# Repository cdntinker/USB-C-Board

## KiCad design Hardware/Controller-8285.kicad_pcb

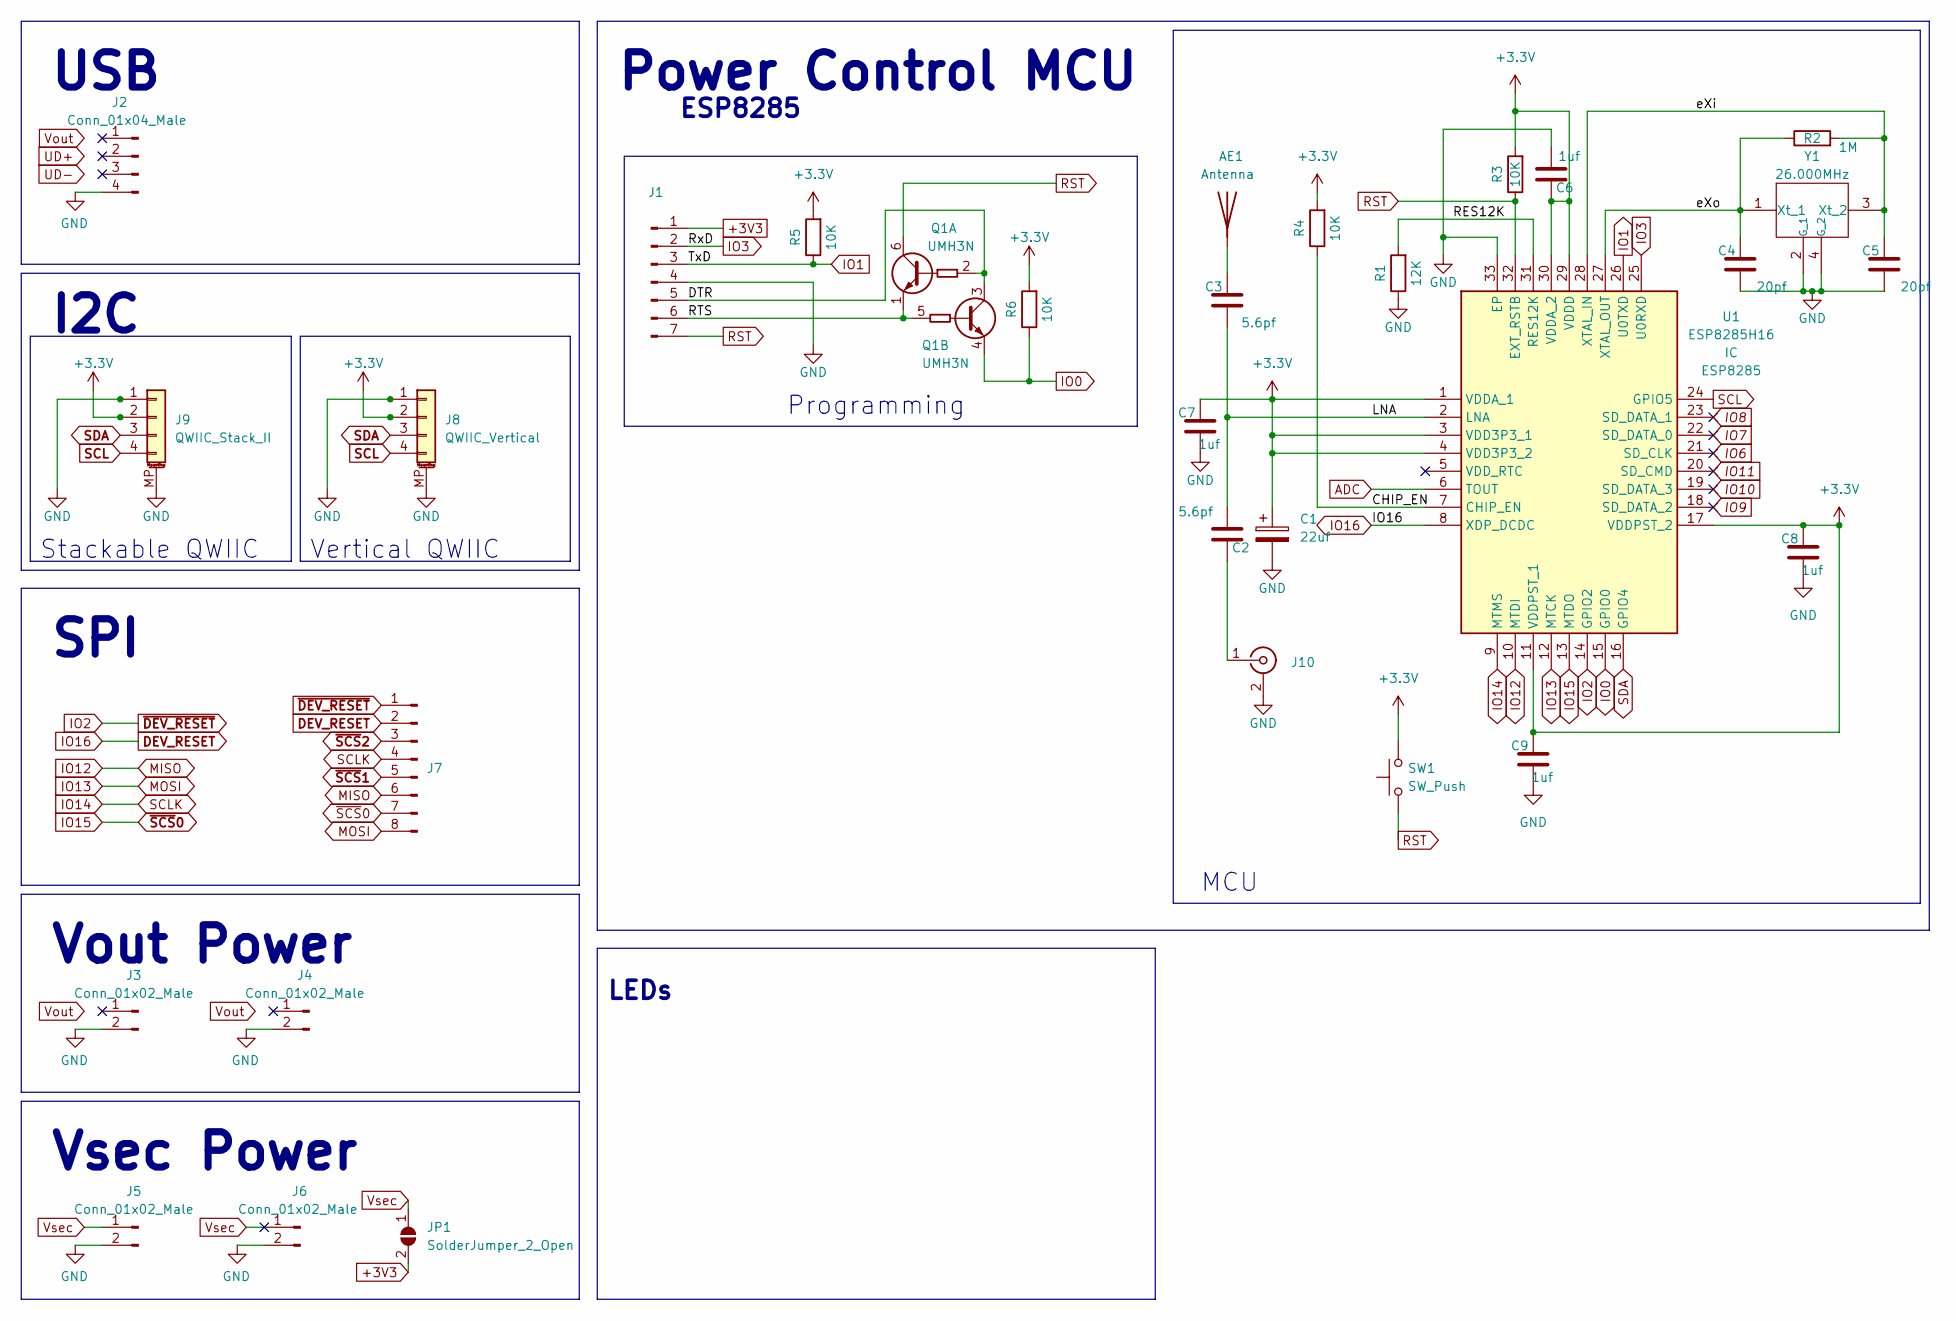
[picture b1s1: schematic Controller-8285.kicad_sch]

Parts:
AE1: Antenna; Texas_SWRA117D_2.4GHz_Left
C1: 22uf; CP_EIA-6032-28-Tantalumm_HandSolder; LCSC C89246
C2, C3: 5.6pf; C_0603_1608Metric; LCSC C162238
C4, C5: 20pf; C_0603_1608Metric; LCSC C325469
C6, C7, C8, C9: 1uf; C_0603_1608Metric; LCSC C559769
J1: Conn_01x07_Male; Board_Stacker_7
J2: Conn_01x04_Male; Board_Stacker_4
J3, J4, J5, J6: Conn_01x02_Male; Board_Stacker_2
J7: Conn_01x08_Male; PinHeader_2x04_P1.27mm_Vertical; LCSC C2881786 + C2684732
J8: QWIIC_Vertical; LCSC C145961
J9: QWIIC_Stack_II; LCSC C145956, C2881513, C2938401
J10: Conn_Coaxial; U.FL_Molex_MCRF_73412-0110_Vertical; LCSC C88373
JP1: SolderJumper_2_Open; SolderJumper-2_P_Open_Rounded_skinny
Q1: UMH3N; SOT-363_SC-70-6; LCSC C62892
R1: 12K; R_0603_1608Metric; LCSC C22790
R2: 1M; R_0603_1608Metric; LCSC C22935
R3, R4, R5, R6: 10K; R_0603_1608Metric; LCSC C25804
SW1: SW_Push; SW_Push_TS273014TP; LCSC C2858276
U1: ESP8285H16; QFN50P500X500X90-33N-D; Manufacturer_Part_Number ESP8285; LCSC C967019
Y1: 26.000MHz; ABM825000MHz10B1UT; LCSC C2149083

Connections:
/CHIP_EN: R4.1, U1.7 (CHIP_EN)
/DTR: J1.5, Q1.2 (B1), Q1.3 (C2)
/LNA: C2.1, C3.1, U1.2 (LNA)
/RES12K: R1.2, U1.31 (RES12K)
/RTS: J1.6, Q1.1 (E1), Q1.5 (B2)
/eXi: C5.2, R2.2, U1.28 (XTAL_IN), Y1.3 (Xt_2)
/eXo: C4.2, R2.1, U1.27 (XTAL_OUT), Y1.1 (Xt_1)
ADC: U1.6 (TOUT)
DEV_RESET: J7.2, U1.8 (XDP_DCDC)
GND: C1.2, C4.1, C5.1, C6.1, C7.1, C8.1, C9.1, J1.4, J2.4, J3.2, J4.2, J5.2, J6.2, J8.1, J8.MP (MountPin), J9.1, J9.MP (MountPin), J10.2 (Ext), R1.1, U1.33 (EP), Y1.2 (G_1), Y1.4 (G_2)
IO0: Q1.4 (E2), R6.1, U1.15 (GPIO0)
IO1: J1.3, R5.1, U1.26 (U0TXD)
IO2: J7.1, U1.14 (GPIO2)
IO3: J1.2, U1.25 (U0RXD)
IO6: U1.21 (SD_CLK)
IO7: U1.22 (SD_DATA_0)
IO8: U1.23 (SD_DATA_1)
IO9: U1.18 (SD_DATA_2)
IO10: U1.19 (SD_DATA_3)
IO11: U1.20 (SD_CMD)
IO12: J7.6, U1.10 (MTDI)
IO13: J7.8, U1.12 (MTCK)
IO14: J7.4, U1.9 (MTMS)
IO15: J7.7, U1.13 (MTDO)
unnamed: AE1.1, C3.2
unnamed: C2.2, J10.1 (In)
RST: J1.7, Q1.6 (C1), R3.1, SW1.1, U1.32 (EXT_RSTB)
SCL: J8.4, J9.4, U1.24 (GPIO5)
SDA: J8.3, J9.3, U1.16 (GPIO4)
Vsec: J5.1, J6.1, JP1.1 (A)
~SCS1: J7.5
~SCS2: J7.3

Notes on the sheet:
I2C
MCU
Vertical QWIIC
Vsec Power
ESP8285
Power Control MCU
USB
SPI
Programming
Vout Power
Stackable QWIIC
LEDs

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
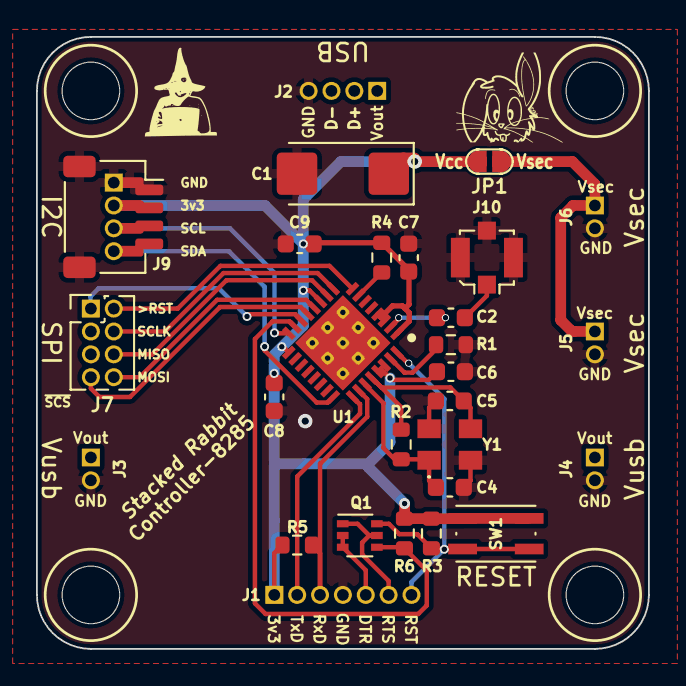
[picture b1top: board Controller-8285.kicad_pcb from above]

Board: 2 copper layers, 34.0 x 34.0 mm, 28 parts (0 on the bottom side), 23 nets.

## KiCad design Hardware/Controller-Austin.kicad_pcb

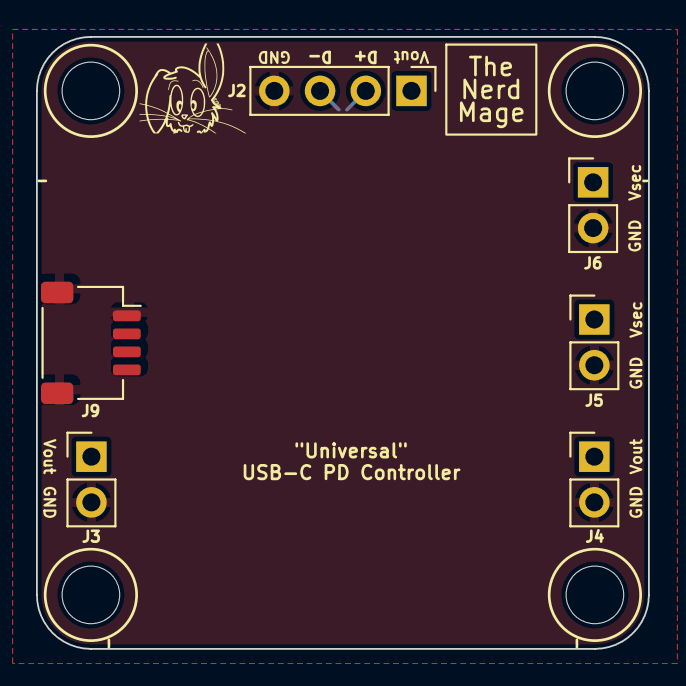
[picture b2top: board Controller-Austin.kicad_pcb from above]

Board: 2 copper layers, 34.0 x 34.0 mm, 6 parts (0 on the bottom side), 3 nets.

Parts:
J2: Conn_01x04_Male; PinHeader_1x04_P2.54mm_Vertical
J3, J4, J5, J6: Conn_01x02_Male; PinHeader_1x02_P2.54mm_Vertical
J9: Conn_01x04_MountingPin; JST_SH_SM04B-SRSS-TB_1x04-1MP_P1.00mm_Horizontal

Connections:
GND: J2.4, J3.2, J4.2, J5.2, J6.2, J9.1, J9.MP (MountPin)
Vout: J2.1, J3.1, J4.1
Vsec: J5.1, J6.1

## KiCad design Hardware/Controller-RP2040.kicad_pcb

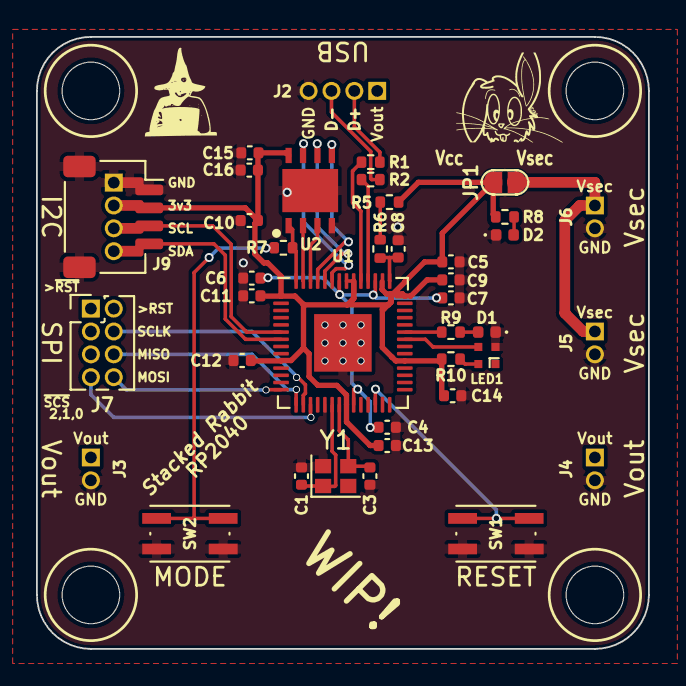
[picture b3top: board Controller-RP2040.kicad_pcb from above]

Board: 2 copper layers, 34.0 x 34.0 mm, 39 parts (0 on the bottom side), 31 nets.

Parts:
C1, C3: 20p; C_0402_1005Metric
C4, C5, C8, C15: 2u2; C_0402_1005Metric
C6, C7, C9, C10, C11, C12, C13, C14, C16: 100n; C_0402_1005Metric
D1, D2: LED; LED_0402_1005Metric
J2: Conn_01x04_Male; Board_Stacker_4
J3, J4, J5, J6: Conn_01x02_Male; Board_Stacker_2
J7: Conn_01x08_Male; PinHeader_2x04_P1.27mm_Vertical
J9: QWIIC_Stack_II
JP1: SolderJumper_2_Open; SolderJumper-2_P_Open_Rounded_skinny
LED1: XL-1010RGBC-WS2812B; XL1010RGBCWS2812B
R1, R2: 27; R_0402_1005Metric
R5: 200; R_0402_1005Metric
R6: 1; R_0402_1005Metric
R7: 1k; R_0402_1005Metric
R8: 2k2; R_0402_1005Metric
R9: 470; R_0402_1005Metric
R10: ???; R_0402_1005Metric
SW1, SW2: SW_Push; SW_Push_TS273014TP
U1: RP2040; QFN-56-1EP_7x7mm_P0.4mm_EP3.2x3.2mm
U2: W25Q32JVXGIQ; SON80P400X400X50-9N
Y1: 12MHz; Crystal_SMD_2016-4Pin_2.0x1.6mm

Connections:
+1V1: C4.2, C6.1, C7.1, U1.23 (DVDD), U1.45 (VREG_VOUT), U1.50 (DVDD)
+3V3: C5.1, C9.1, C10.1, C11.1, C12.1, C13.1, C14.1, C15.2, C16.1, J9.2, JP1.2 (B), R5.2, R8.1, R10.1, U1.1 (IOVDD), U1.10 (IOVDD), U1.22 (IOVDD), U1.33 (IOVDD), U1.42 (IOVDD), U1.44 (VREG_IN), U1.48 (USB_VDD), U1.49 (IOVDD), U2.8 (VCC)
/USB_DM: R2.2, U1.46 (USB_DM)
/USB_DP: R1.2, U1.47 (USB_DP)
/Xout: C3.1, U1.21 (XOUT), Y1.3
ADC_REF: R5.1, R6.2
BootMode: R7.2, SW2.2
GND: C1.2, C3.2, C4.1, C5.2, C6.2, C7.2, C8.1, C9.2, C10.2, C11.2, C12.2, C13.2, C14.2, C15.1, C16.2, D1.1 (K), D2.1 (K), J2.4, J3.2, J4.2, J5.2, J6.2, J9.1, J9.MP (MountPin), LED1.3 (GND), SW1.1, SW2.1, U1.19 (TESTEN), U1.57 (GND), U2.4 (GND), U2.9 (EP), Y1.4
MISO: J7.6, U1.15 (GPIO12)
MOSI: J7.8, U1.14 (GPIO11)
unnamed: C1.1, U1.20 (XIN), Y1.1
unnamed: C8.2, R6.1, U1.43 (ADC_AVDD)
unnamed: D1.2 (A), R9.2
unnamed: D2.2 (A), R8.2
unnamed: LED1.2 (VDD), R10.2
QSPI SS: R7.1, U1.56 (QSPI_SS), U2.1 (~CS)
QSPI_SCLK: U1.52 (QSPI_SCLK), U2.6 (CLK)
QSPI_SD0: U1.53 (QSPI_SD0), U2.5 (DI(IO0))
QSPI_SD1: U1.55 (QSPI_SD1), U2.2 (DO(IO1))
QSPI_SD2: U1.54 (QSPI_SD2), U2.3 (IO2)
QSPI_SD3: U1.51 (QSPI_SD3), U2.7 (IO3)
Reset: SW1.2, U1.26 (RUN)
SCL: J9.4, U1.7 (GPIO5)
SCLK: J7.4, U1.16 (GPIO13)
SDA: J9.3, U1.6 (GPIO4)
UD+: J2.2, R1.1
UD-: J2.3, R2.1
Vsec: J5.1, J6.1, JP1.1 (A)
io14: J7.7, U1.17 (GPIO14)
io24: LED1.4 (DI), U1.36 (GPIO24)
io25: R9.1, U1.37 (GPIO25)

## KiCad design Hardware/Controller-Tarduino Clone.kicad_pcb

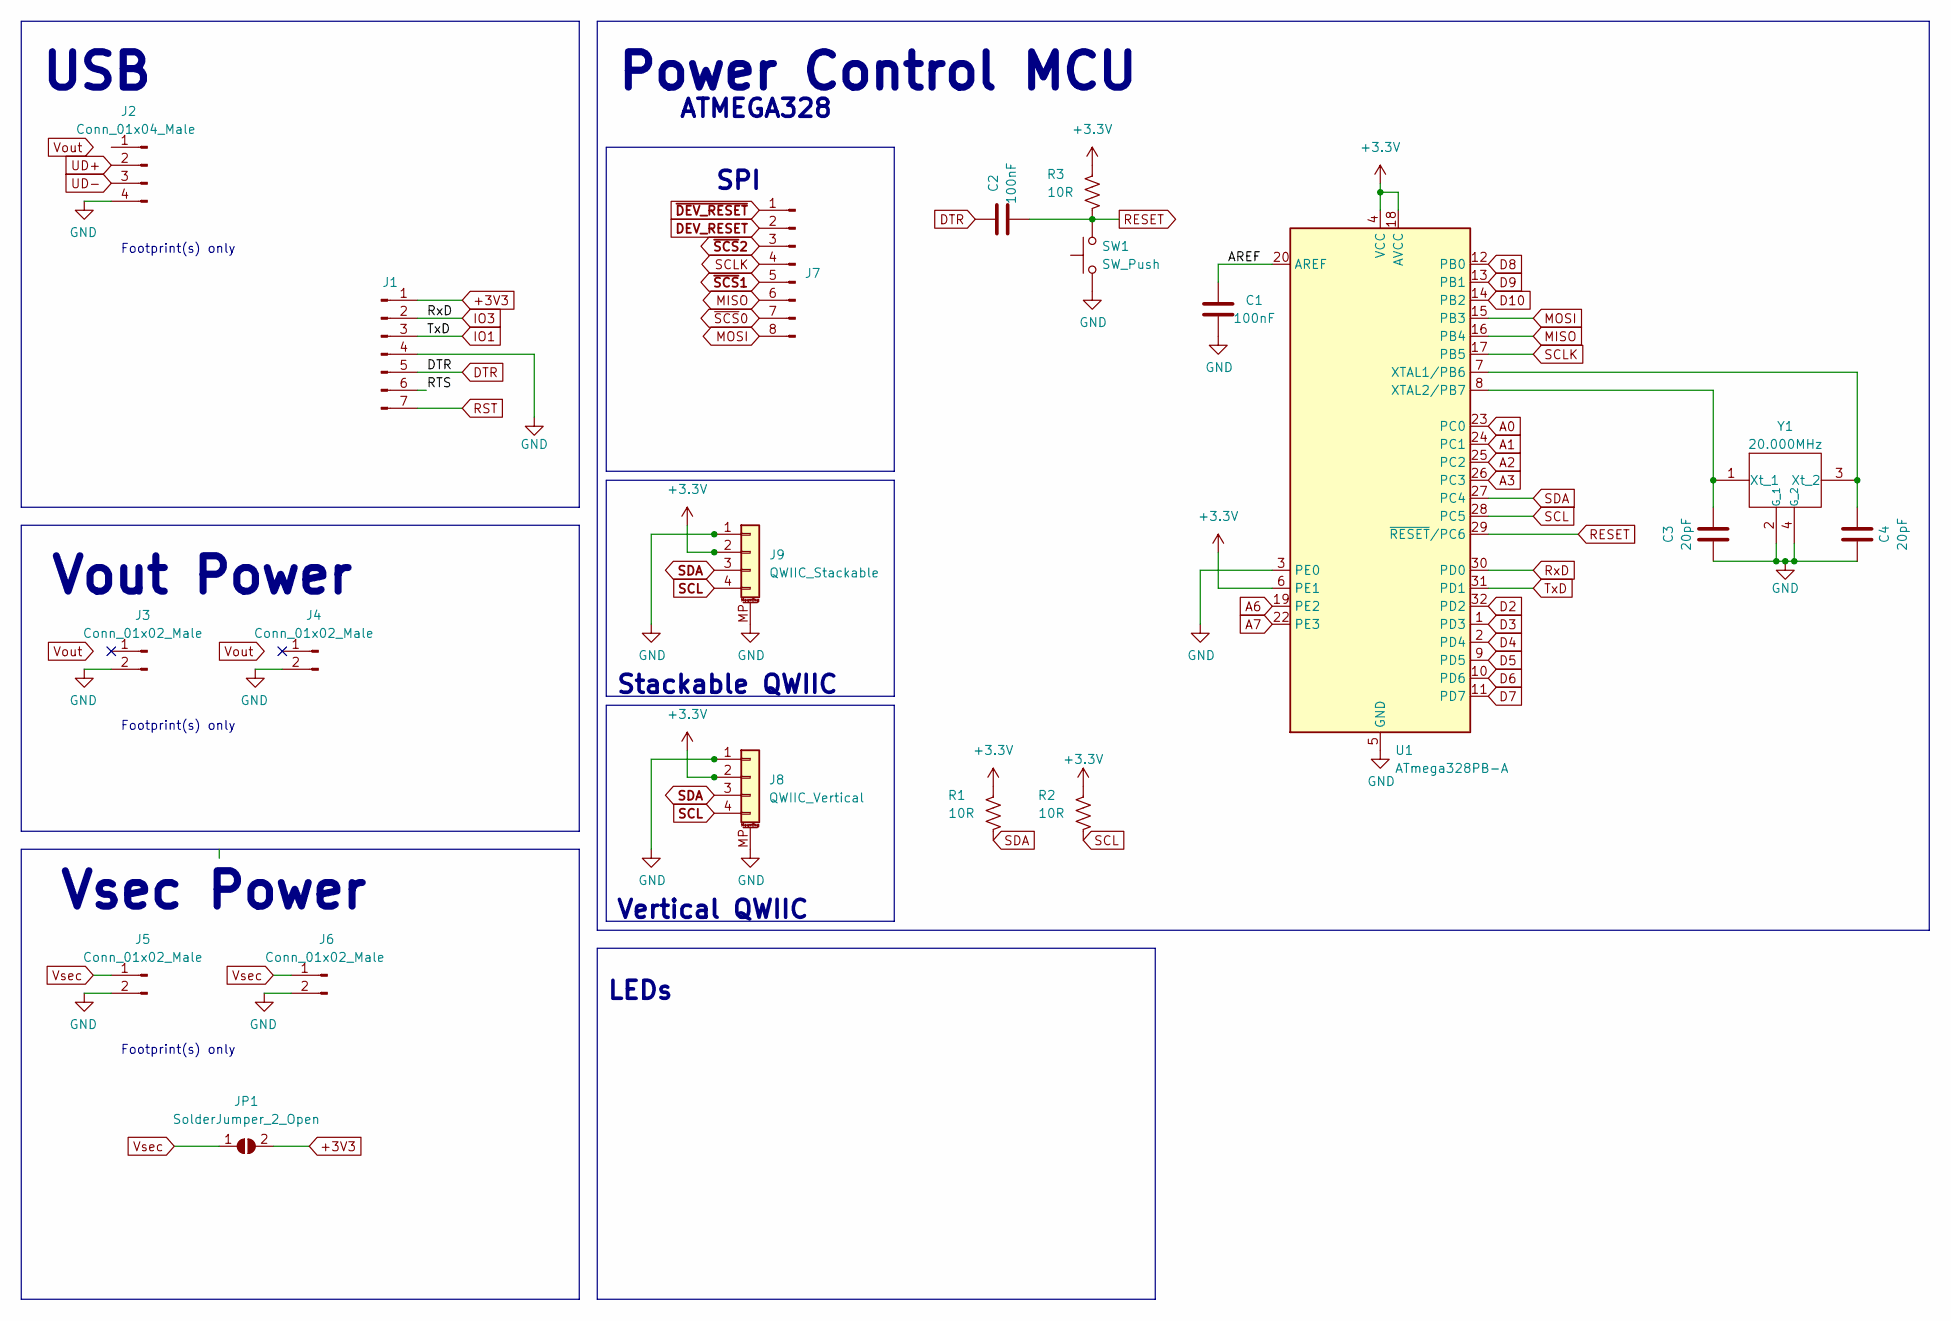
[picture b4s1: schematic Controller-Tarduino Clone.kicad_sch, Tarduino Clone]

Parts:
C1, C2: 100nF; C_0603_1608Metric; LCSC C14663
C3, C4: 20pF; C_0603_1608Metric; LCSC C105621
J1: Conn_01x07_Male; Board_Stacker_7
J2: Conn_01x04_Male; Board_Stacker_4
J3, J4, J5, J6: Conn_01x02_Male; Board_Stacker_2
J7: Conn_01x08_Male; PinHeader_2x04_P1.27mm_Vertical; LCSC C2881786 + C2684732
J8: QWIIC_Vertical; LCSC C145961
J9: QWIIC_Stackable; QWIIC_Stack_II; LCSC C145956, C2881513, C2938401
JP1: SolderJumper_2_Open; SolderJumper-2_P_Open_Rounded_skinny
R1, R2, R3: 10R; R_0603_1608Metric; LCSC C103222
SW1: SW_Push; SW_Push_TS273014TP; LCSC C2858276
U1: ATmega328PB-A; TQFP-32_7x7mm_P0.8mm
Y1: 20.000MHz; ABM825000MHz10B1UT; LCSC C7294562

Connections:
/AREF: C1.2, U1.20 (AREF)
/RTS: J1.6
A0: U1.23 (PC0)
A1: U1.24 (PC1)
A2: U1.25 (PC2)
A3: U1.26 (PC3)
A6: U1.19 (PE2)
A7: U1.22 (PE3)
D2: U1.32 (PD2)
D3: U1.1 (PD3)
D4: U1.2 (PD4)
D5: U1.9 (PD5)
D6: U1.10 (PD6)
D7: U1.11 (PD7)
D8: U1.12 (PB0)
D9: U1.13 (PB1)
D10: U1.14 (PB2)
DEV_RESET: J7.2
DTR: C2.2, J1.5
GND: C1.1, C3.1, C4.1, J1.4, J2.4, J3.2, J4.2, J5.2, J6.2, J8.1, J8.MP (MountPin), J9.1, J9.MP (MountPin), SW1.1, U1.3 (PE0), U1.5 (GND), U1.21 (GND), Y1.2 (G_1), Y1.4 (G_2)
IO1: J1.3, U1.31 (PD1)
IO3: J1.2, U1.30 (PD0)
MISO: J7.6, U1.16 (PB4)
MOSI: J7.8, U1.15 (PB3)
unnamed: C3.2, U1.8 (XTAL2/PB7), Y1.1 (Xt_1)
unnamed: C4.2, U1.7 (XTAL1/PB6), Y1.3 (Xt_2)
RESET: C2.1, R3.1, SW1.2, U1.29 (~RESET/PC6)
RST: J1.7
SCL: J8.4, J9.4, R2.1, U1.28 (PC5)
SCLK: J7.4, U1.17 (PB5)
SDA: J8.3, J9.3, R1.1, U1.27 (PC4)
UD+: J2.2
UD-: J2.3
Vsec: J5.1, J6.1, JP1.1 (A)
~DEV_RESET: J7.1
~SCS0: J7.7
~SCS1: J7.5
~SCS2: J7.3

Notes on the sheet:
Vsec Power
Vout Power
Footprint(s) only
Vertical QWIIC
Stackable QWIIC
ATMEGA328
USB
SPI
Power Control MCU
LEDs

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
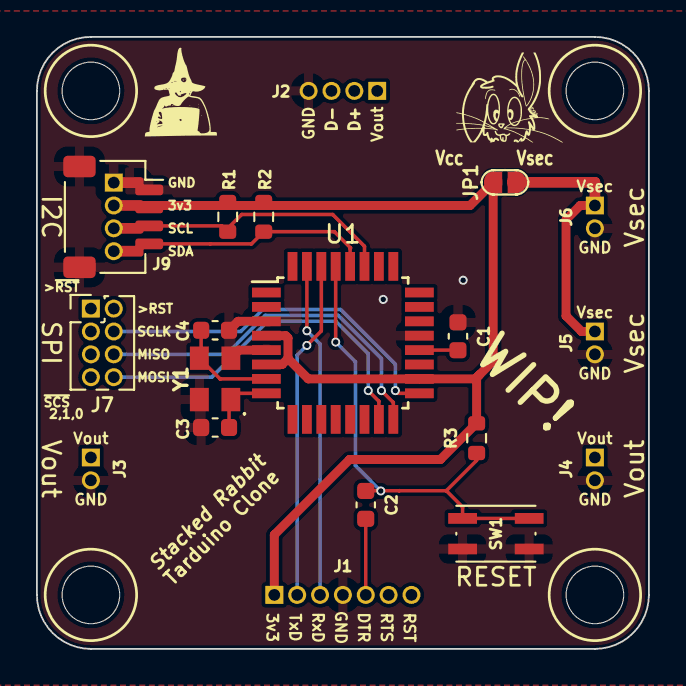
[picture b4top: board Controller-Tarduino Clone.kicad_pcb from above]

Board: 2 copper layers, 34.0 x 34.0 mm, 19 parts (0 on the bottom side), 15 nets.

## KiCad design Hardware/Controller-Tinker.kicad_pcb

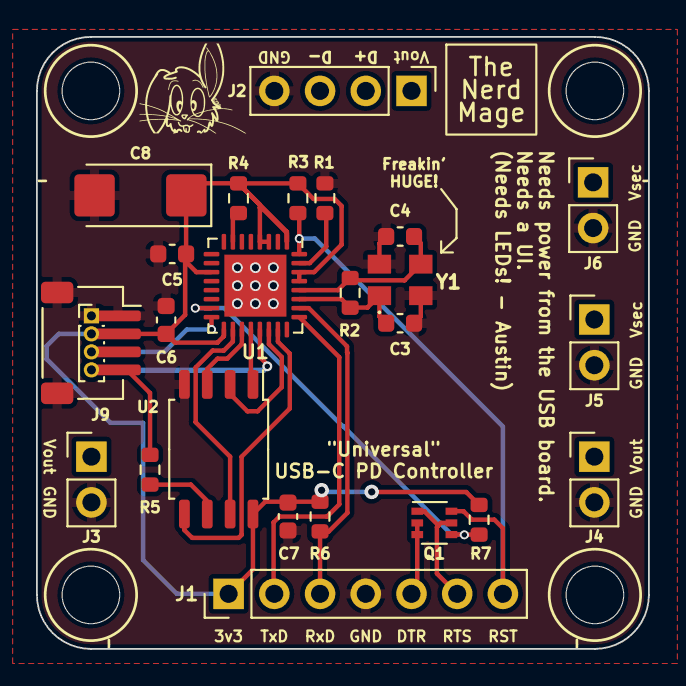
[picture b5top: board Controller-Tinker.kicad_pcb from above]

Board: 2 copper layers, 34.0 x 34.0 mm, 24 parts (0 on the bottom side), 20 nets.

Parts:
C3, C4: 10pf; C_0603_1608Metric
C5: TBD (NC); C_0603_1608Metric
C6: 1uf; C_0603_1608Metric
C7: 100nf; C_0603_1608Metric
C8: 22uf; CP_EIA-6032-28-Tantalumm_HandSolder
J1: Conn_01x07_Male; PinHeader_1x07_P2.54mm_Vertical
J2: Conn_01x04_Male; PinHeader_1x04_P2.54mm_Vertical
J3, J4, J5, J6: Conn_01x02_Male; PinHeader_1x02_P2.54mm_Vertical
J9: QWIIC_Stackable
Q1: UMH3N; SOT-363_SC-70-6
R1: 12K; R_0603_1608Metric
R2: 1M; R_0603_1608Metric
R3, R4, R6, R7: 10K; R_0603_1608Metric
R5: 200R; R_0603_1608Metric
U1: ESP8266EX; QFN-32-1EP_5x5mm_P0.5mm_EP3.45x3.45mm
U2: SST25VF016B-50-4I-S2AF; SOIC-8_5.275x5.275mm_P1.27mm
Y1: 26.000MHz; ABM825000MHz10B1UT

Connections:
+3V3: C5.1, C6.1, C7.1, C8.1, J1.1, J9.2, R3.2, R4.2, R6.2, R7.2, U1.1 (VDDA), U1.3 (VDD3P3), U1.4 (VDD3P3), U1.11 (VDDPST), U1.17 (VDDPST), U1.29 (VDDD), U1.30 (VDDA), U2.8 (VDD)
/DTR: J1.5, Q1.2 (B1), Q1.3 (C2)
/RTS: J1.6, Q1.1 (E1), Q1.5 (B2)
/eXi: C4.2, R2.2, U1.28 (XTAL_IN), Y1.3 (Xt_2)
/eXo: C3.2, R2.1, U1.27 (XTAL_OUT), Y1.1 (Xt_1)
GND: C3.1, C4.1, C5.2, C6.2, C7.2, C8.2, J1.4, J2.4, J3.2, J4.2, J5.2, J6.2, J9.1, J9.MP (MountPin), R1.1, U1.33 (GND), U2.4 (VSS), Y1.2 (G_1), Y1.4 (G_2)
IO0: Q1.4 (E2), R7.1, U1.15 (GPIO0)
IO1: J1.3, R6.1, U1.26 (U0TXD)
IO3: J1.2, U1.25 (U0RXD)
IO7: U1.22 (SDIO_DATA_0), U2.2 (SO)
IO8: U1.23 (SDIO_DATA_1), U2.5 (SI)
IO9: U1.18 (SDIO_DATA_2), U2.7 (HOLD#)
IO10: U1.19 (SDIO_DATA_3), U2.3 (WP#)
IO11: U1.20 (SDIO_CMD), U2.1 (CE#)
unnamed: R1.2, U1.31 (RES12K)
unnamed: R4.1, U1.7 (CHIP_PU)
unnamed: R5.2, U2.6 (SCK)
RST: J1.7, Q1.6 (C1), R3.1, U1.32 (~EXT_RSTB)
SCL: J9.4, R5.1, U1.21 (SDIO_CLK)
SDA: J9.3, U1.16 (GPIO4)
